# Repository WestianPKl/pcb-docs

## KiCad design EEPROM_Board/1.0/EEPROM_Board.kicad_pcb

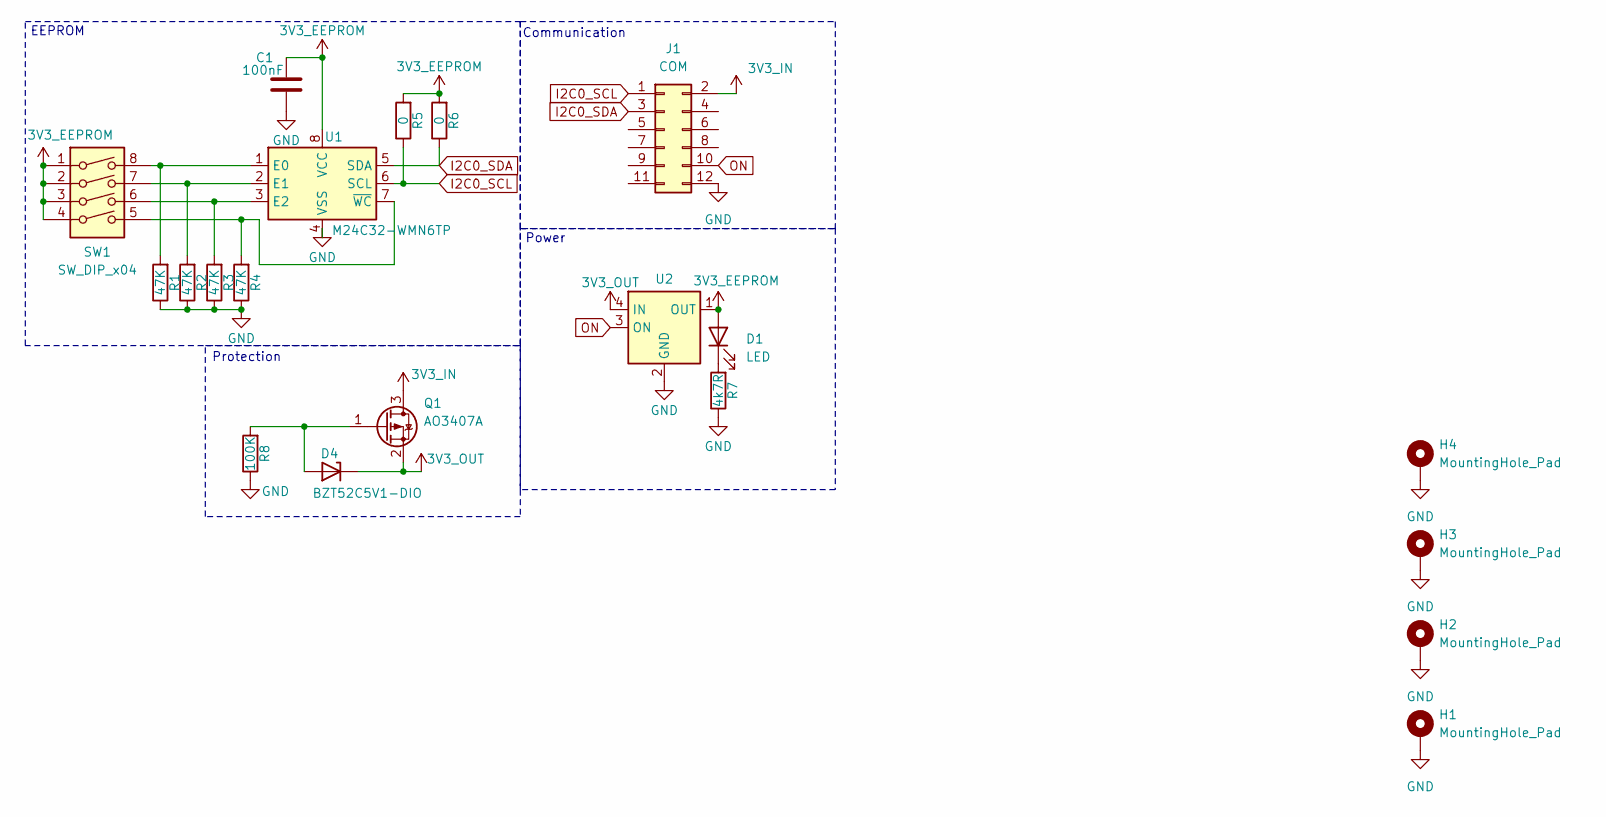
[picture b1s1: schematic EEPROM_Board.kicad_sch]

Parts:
C1: 100nF; C_0805_2012Metric
D1: LED; LED_0805_2012Metric
D4: BZT52C5V1-DIO; D_SOD-123F
H1, H2, H3, H4: MountingHole_Pad; MountingHole_3.2mm_M3_DIN965_Pad
J1: COM; PinHeader_2x06_P2.54mm_Vertical
Q1: AO3407A; SOT-23
R1, R2, R3, R4: 47K; R_0805_2012Metric
R5, R6: 0; R_0805_2012Metric
R7: 4k7R; R_0805_2012Metric
R8: 100K; R_0805_2012Metric
SW1: SW_DIP_x04; SW_DIP_SPSTx04_Slide_9.78x12.34mm_W7.62mm_P2.54mm
U1: M24C32-WMN6TP; SOIC-8_3.9x4.9mm_P1.27mm
U2: SIP32431DR3-T1GE3; SOT-363_SC-70-6

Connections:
3V3_EEPROM: C1.1, D1.2 (A), R5.2, R6.2, SW1.1, SW1.2, SW1.3, SW1.4, U1.8 (VCC), U2.1 (OUT)
3V3_IN: J1.2, Q1.3 (D)
3V3_OUT: D4.1 (K), Q1.2 (S), U2.4 (IN)
GND: C1.2, H1.1, H2.1, H3.1, H4.1, J1.12, R1.1, R2.1, R3.1, R4.1, R7.1, R8.1, U1.4 (VSS), U2.2 (GND), U2.5 (GND)
I2C0_SCL: J1.1, R5.1, U1.6 (SCL)
I2C0_SDA: J1.3, R6.1, U1.5 (SDA)
unnamed: D1.1 (K), R7.2
unnamed: D4.2 (A), Q1.1 (G), R8.2
unnamed: R1.2, SW1.8, U1.1 (E0)
unnamed: R2.2, SW1.7, U1.2 (E1)
unnamed: R3.2, SW1.6, U1.3 (E2)
unnamed: R4.2, SW1.5, U1.7 (~WC)
ON: J1.10, U2.3 (ON)

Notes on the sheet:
Communication
Power
EEPROM
Protection

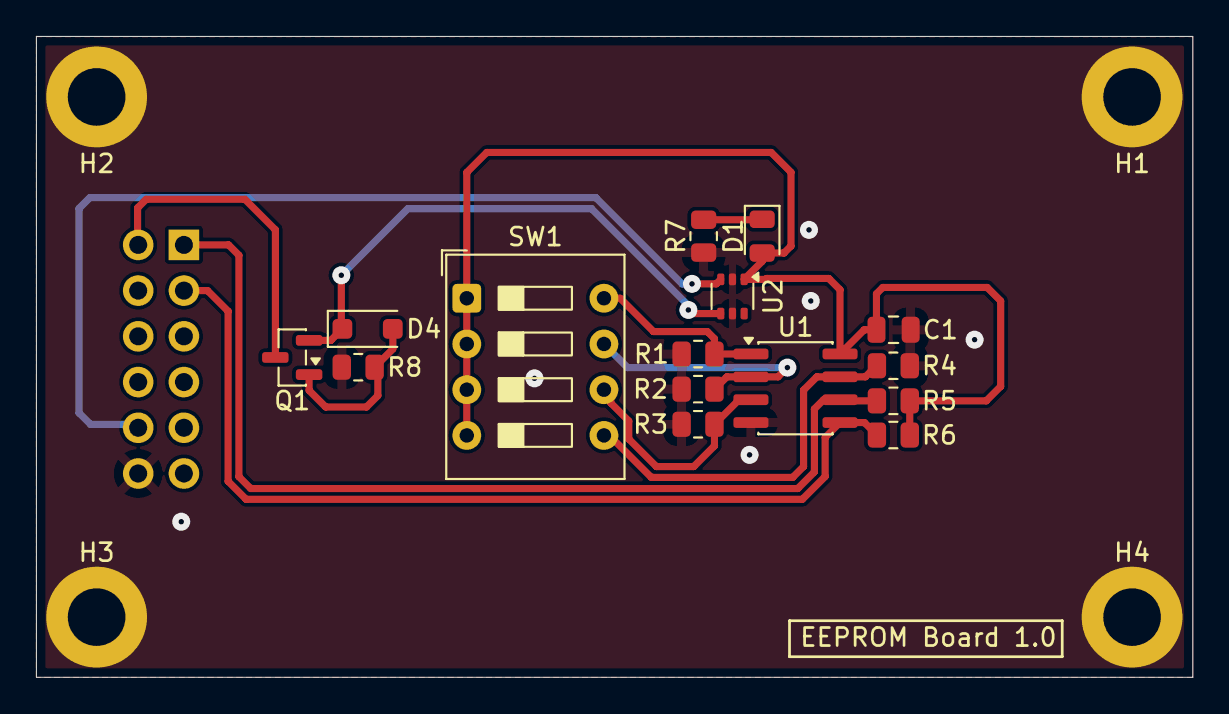
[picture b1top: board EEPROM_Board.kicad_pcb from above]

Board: 2 copper layers, 64.2 x 35.6 mm, 20 parts (1 on the bottom side), 13 nets.

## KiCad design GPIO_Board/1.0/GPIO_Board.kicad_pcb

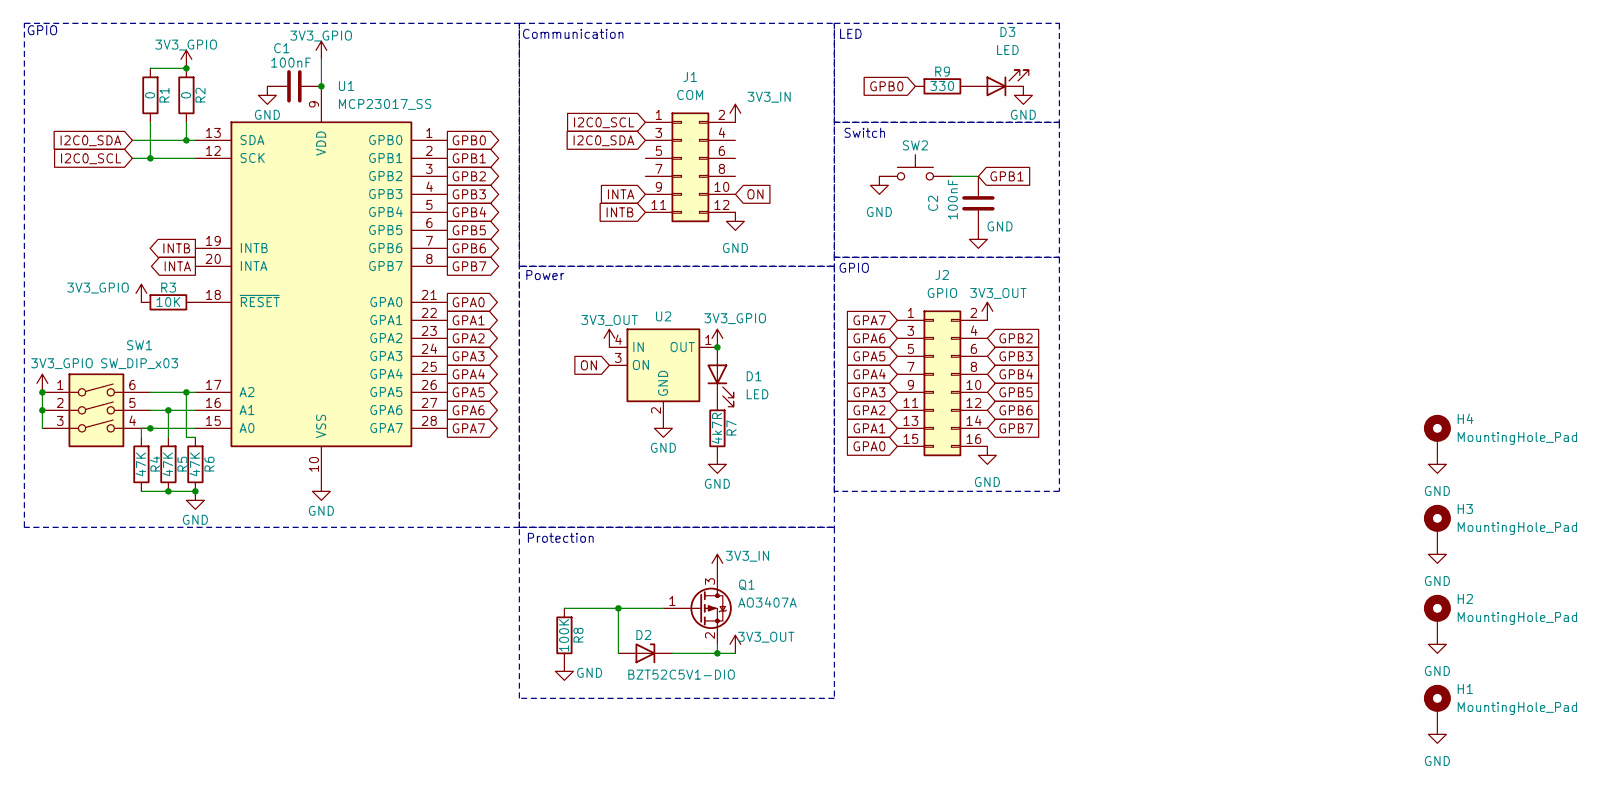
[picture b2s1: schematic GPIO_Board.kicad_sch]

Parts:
C1, C2: 100nF; C_0805_2012Metric
D1, D3: LED; LED_0805_2012Metric
D2: BZT52C5V1-DIO; D_SOD-123F
H1, H2, H3, H4: MountingHole_Pad; MountingHole_3.2mm_M3_DIN965_Pad
J1: COM; PinHeader_2x06_P2.54mm_Vertical
J2: GPIO; PinHeader_2x08_P2.54mm_Vertical
Q1: AO3407A; SOT-23
R1, R2: 0; R_0805_2012Metric
R3: 10K; R_0805_2012Metric
R4, R5, R6: 47K; R_0805_2012Metric
R7: 4k7R; R_0805_2012Metric
R8: 100K; R_0805_2012Metric
R9: 330; R_0805_2012Metric
SW1: SW_DIP_x03; SW_DIP_SPSTx03_Slide_9.78x9.8mm_W7.62mm_P2.54mm
SW2: Tact Switch 6x6mm / 13mm; SW_PUSH_6mm
U1: MCP23017_SS; SSOP-28_5.3x10.2mm_P0.65mm
U2: SIP32431DR3-T1GE3; SOT-363_SC-70-6

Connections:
3V3_GPIO: C1.1, D1.2 (A), R1.2, R2.2, R3.2, SW1.1, SW1.2, SW1.3, U1.9 (VDD), U2.1 (OUT)
3V3_IN: J1.2, Q1.3 (D)
3V3_OUT: D2.1 (K), J2.2, Q1.2 (S), U2.4 (IN)
GND: C1.2, C2.2, D3.1 (K), H1.1, H2.1, H3.1, H4.1, J1.12, J2.16, R4.1, R5.1, R6.1, R7.1, R8.1, SW2.1, U1.10 (VSS), U2.2 (GND), U2.5 (GND)
GPA0: J2.15, U1.21 (GPA0)
GPA1: J2.13, U1.22 (GPA1)
GPA2: J2.11, U1.23 (GPA2)
GPA3: J2.9, U1.24 (GPA3)
GPA4: J2.7, U1.25 (GPA4)
GPA5: J2.5, U1.26 (GPA5)
GPA6: J2.3, U1.27 (GPA6)
GPA7: J2.1, U1.28 (GPA7)
GPB0: R9.2, U1.1 (GPB0)
GPB1: C2.1, SW2.2, U1.2 (GPB1)
GPB2: J2.4, U1.3 (GPB2)
GPB3: J2.6, U1.4 (GPB3)
GPB4: J2.8, U1.5 (GPB4)
GPB5: J2.10, U1.6 (GPB5)
GPB6: J2.12, U1.7 (GPB6)
GPB7: J2.14, U1.8 (GPB7)
I2C0_SCL: J1.1, R1.1, U1.12 (SCK)
I2C0_SDA: J1.3, R2.1, U1.13 (SDA)
INTA: J1.9, U1.20 (INTA)
INTB: J1.11, U1.19 (INTB)
unnamed: D1.1 (K), R7.2
unnamed: D2.2 (A), Q1.1 (G), R8.2
unnamed: D3.2 (A), R9.1
unnamed: R4.2, SW1.4, U1.15 (A0)
unnamed: R5.2, SW1.5, U1.16 (A1)
unnamed: R6.2, SW1.6, U1.17 (A2)
unnamed: R3.1, U1.18 (~RESET)
ON: J1.10, U2.3 (ON)

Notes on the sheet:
LED
Protection
Communication
GPIO
Switch
Power

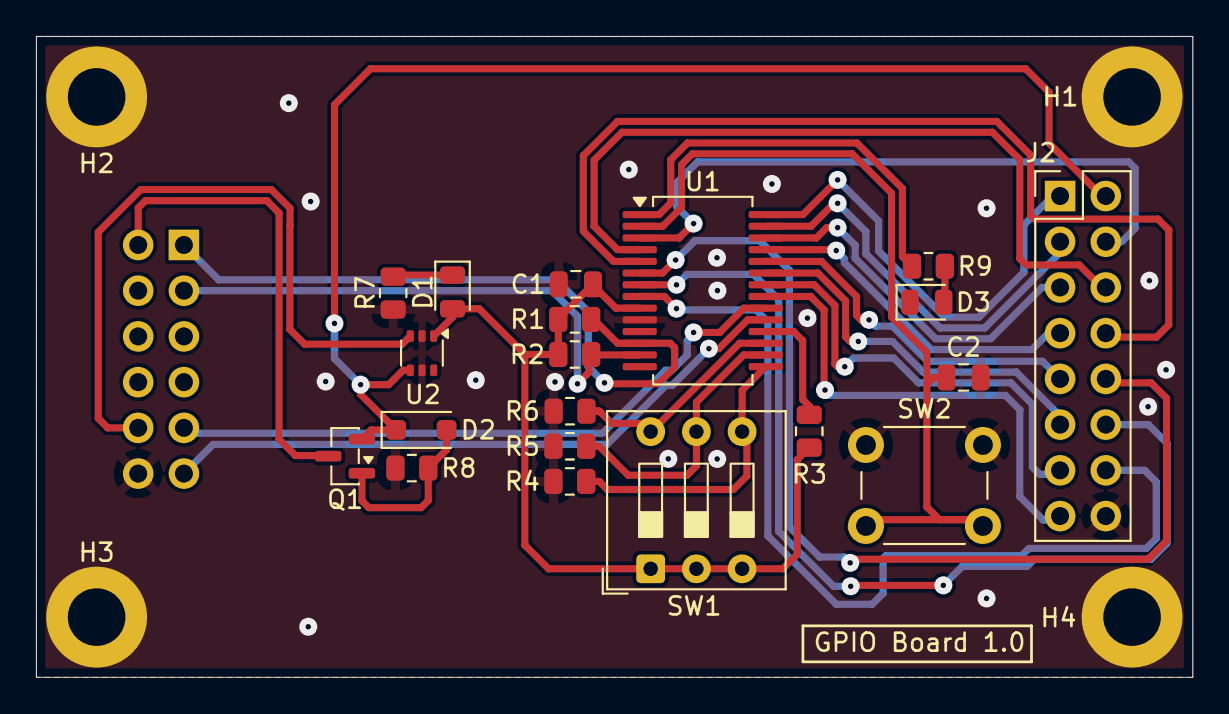
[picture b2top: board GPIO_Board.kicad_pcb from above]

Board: 2 copper layers, 64.2 x 35.6 mm, 25 parts (1 on the bottom side), 32 nets.

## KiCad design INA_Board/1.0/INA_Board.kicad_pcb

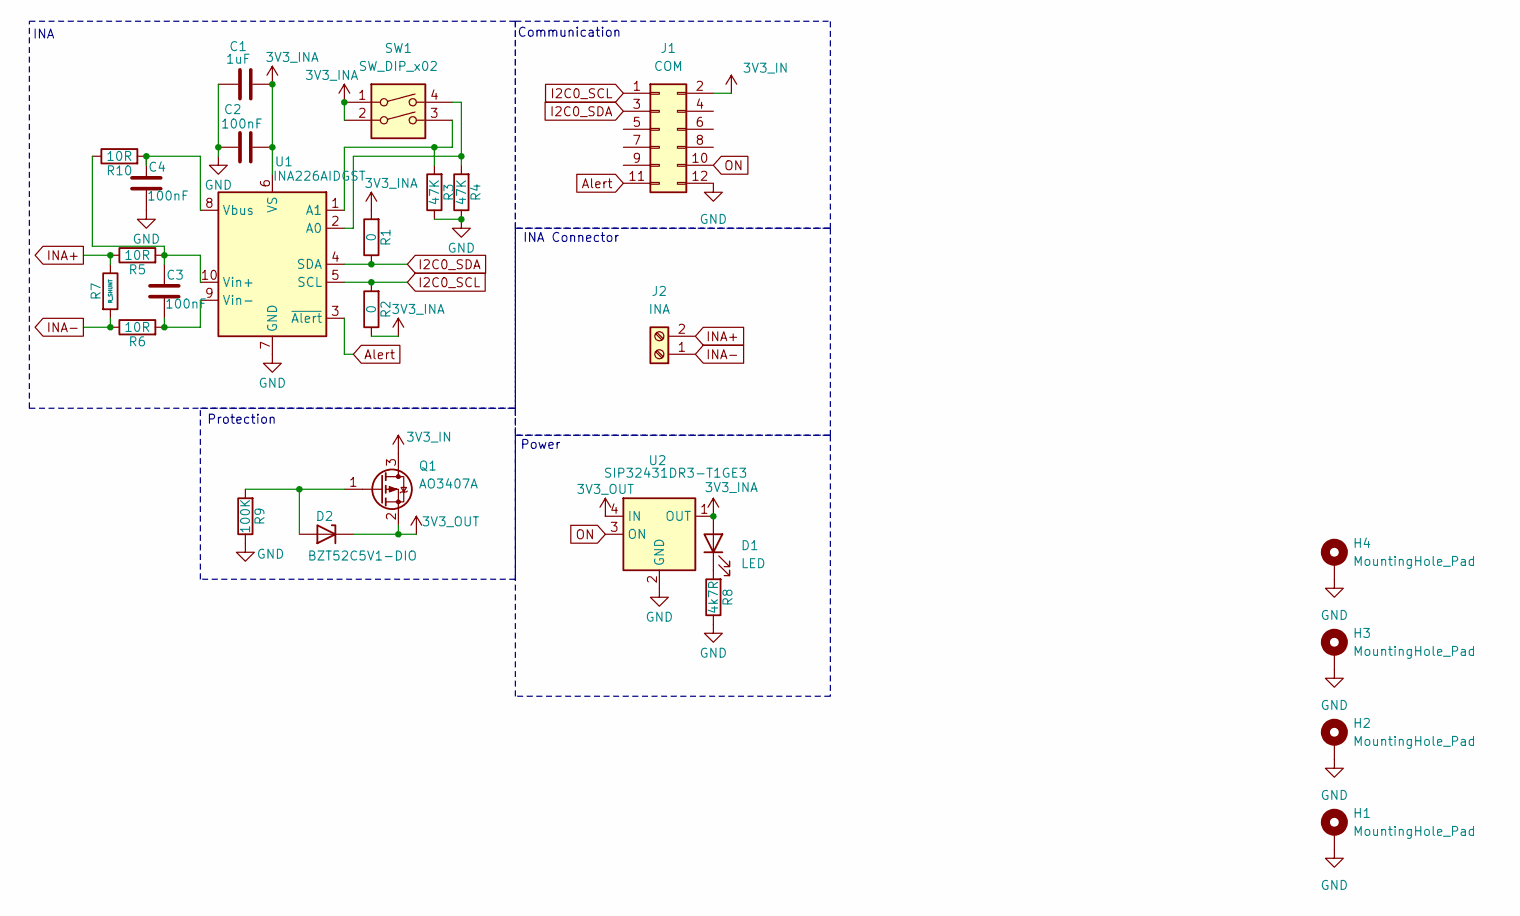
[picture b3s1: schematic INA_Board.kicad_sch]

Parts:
C1: 1uF; C_0603_1608Metric
C2, C3, C4: 100nF; C_0805_2012Metric
D1: LED; LED_0805_2012Metric
D2: BZT52C5V1-DIO; D_SOD-123F
H1, H2, H3, H4: MountingHole_Pad; MountingHole_3.2mm_M3_DIN965_Pad
J1: COM; PinHeader_2x06_P2.54mm_Vertical
J2: INA; TerminalBlock_Phoenix_MKDS-1,5-2_1x02_P5.00mm_Horizontal
Q1: AO3407A; SOT-23
R1, R2: 0; R_0805_2012Metric
R3, R4: 47K; R_0805_2012Metric
R5, R6, R10: 10R; R_0805_2012Metric
R7: R_SHUNT; R_2512_6332Metric
R8: 4k7R; R_0805_2012Metric
R9: 100K; R_0805_2012Metric
SW1: SW_DIP_x02; SW_DIP_SPSTx02_Slide_9.78x7.26mm_W7.62mm_P2.54mm
U1: INA226AIDGST; VSSOP-10_3x3mm_P0.5mm
U2: SIP32431DR3-T1GE3; SOT-363_SC-70-6

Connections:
3V3_IN: J1.2, Q1.3 (D)
3V3_INA: C1.1, C2.1, D1.2 (A), R1.2, R2.1, SW1.1, SW1.2, U1.6 (VS), U2.1 (OUT)
3V3_OUT: D2.1 (K), Q1.2 (S), U2.4 (IN)
Alert: J1.11, U1.3 (~Alert)
GND: C1.2, C2.2, C4.1, H1.1, H2.1, H3.1, H4.1, J1.12, R3.1, R4.1, R8.1, R9.1, U1.7 (GND), U2.2 (GND), U2.5 (GND)
I2C0_SCL: J1.1, R2.2, U1.5 (SCL)
I2C0_SDA: J1.3, R1.1, U1.4 (SDA)
INA+: J2.2, R5.1, R7.1
INA-: J2.1, R6.1, R7.2
unnamed: D1.1 (K), R8.2
unnamed: D2.2 (A), Q1.1 (G), R9.2
unnamed: R4.2, SW1.4, U1.2 (A0)
unnamed: R3.2, SW1.3, U1.1 (A1)
unnamed: C4.2, R10.2, U1.8 (Vbus)
unnamed: C3.2, R5.2, R10.1, U1.10 (Vin+)
unnamed: C3.1, R6.2, U1.9 (Vin-)
ON: J1.10, U2.3 (ON)

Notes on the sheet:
Protection
INA Connector
Power
INA
Communication

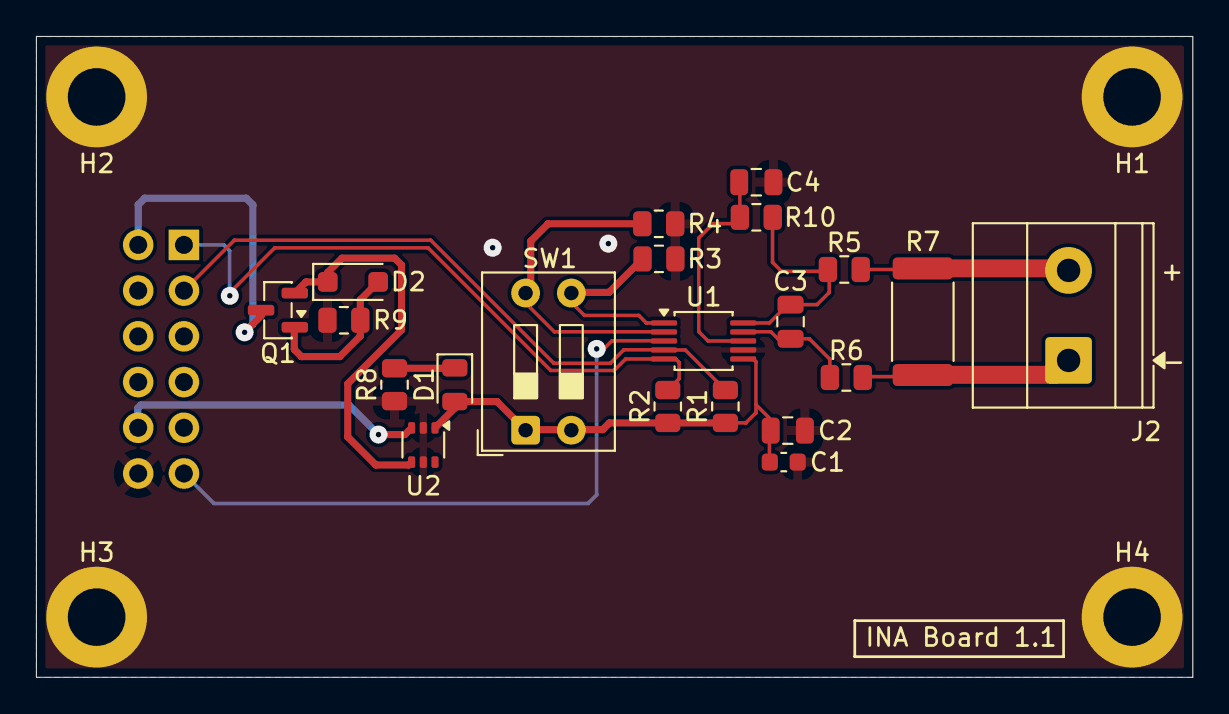
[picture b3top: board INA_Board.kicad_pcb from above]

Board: 2 copper layers, 64.2 x 35.6 mm, 26 parts (1 on the bottom side), 17 nets.

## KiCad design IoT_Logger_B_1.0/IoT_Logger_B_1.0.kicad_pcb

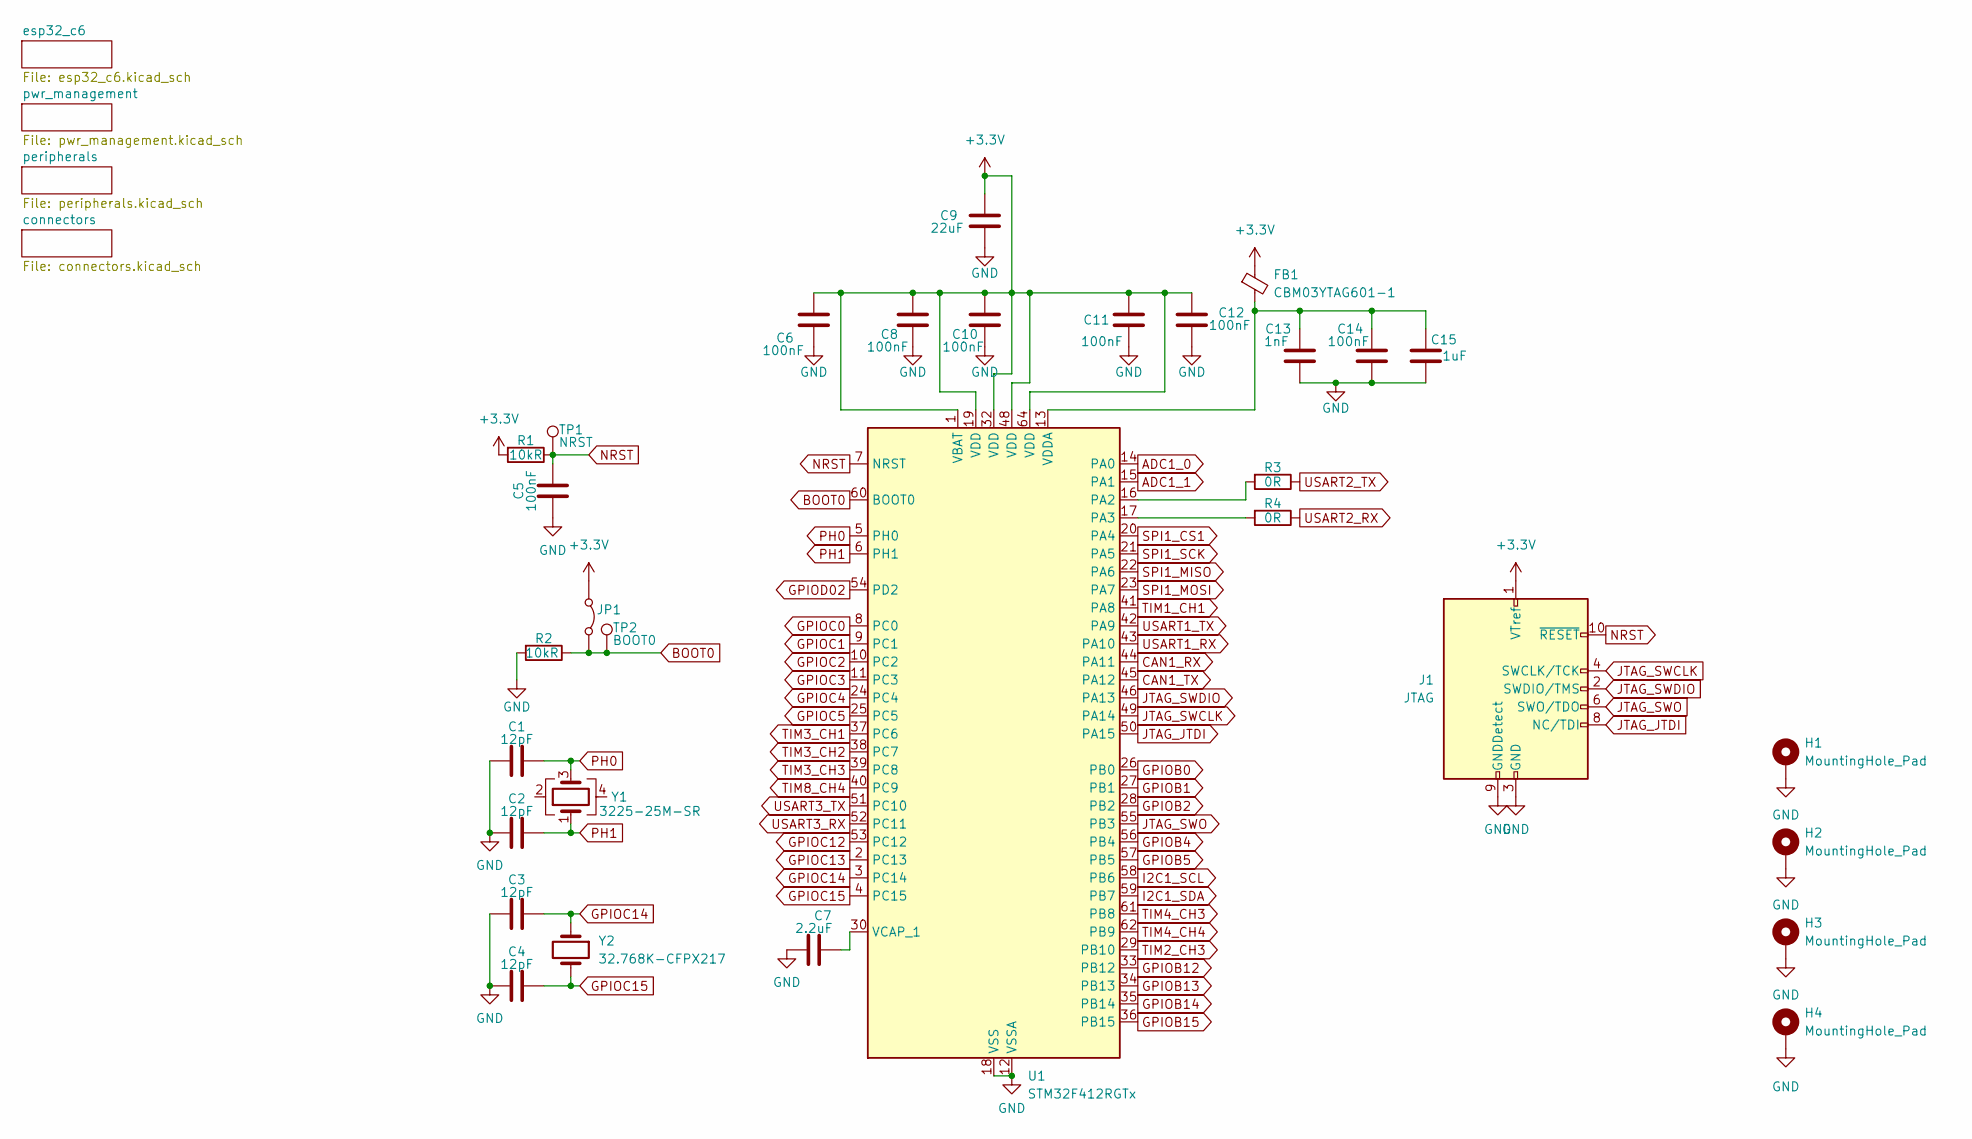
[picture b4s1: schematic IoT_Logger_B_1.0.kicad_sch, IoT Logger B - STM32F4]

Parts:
C1, C2, C3, C4: 12pF; C_0603_1608Metric
C5, C6, C8, C10, C11, C12, C14: 100nF; C_0603_1608Metric
C7: 2.2uF; C_0603_1608Metric
C9: 22uF; C_0603_1608Metric
C13: 1nF; C_0603_1608Metric
C15: 1uF; C_0603_1608Metric
FB1: CBM03YTAG601-1; L_0603_1608Metric
H1, H2, H3, H4: MountingHole_Pad; MountingHole_3.2mm_M3_DIN965_Pad
J1: JTAG; PinHeader_2x05_P1.27mm_Vertical
JP1: Jumper_2_Bridged; PinHeader_1x02_P2.54mm_Vertical
R1, R2: 10kR; R_0603_1608Metric
R3, R4: 0R; R_0603_1608Metric
TP1: NRST; TestPoint_Pad_D1.5mm
TP2: BOOT0; TestPoint_Pad_D1.5mm
U1: STM32F412RGTx; LQFP-64_10x10mm_P0.5mm
Y1: 3225-25M-SR; Crystal_SMD_3225-4Pin_3.2x2.5mm
Y2: 32.768K-CFPX217; Crystal_SMD_3215-2Pin_3.2x1.5mm

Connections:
+3.3V: C6.1, C8.1, C9.1, C10.1, C11.1, C12.1, FB1.1, J1.1 (VTref), JP1.1 (A), R1.2, U1.1 (VBAT), U1.19 (VDD), U1.32 (VDD), U1.48 (VDD), U1.64 (VDD); also elsewhere on the board
ADC1_0: U1.14 (PA0); also elsewhere on the board
ADC1_1: U1.15 (PA1); also elsewhere on the board
BOOT0: JP1.2 (B), R2.1, TP2.1, U1.60 (BOOT0); also elsewhere on the board
CAN1_RX: U1.44 (PA11); also elsewhere on the board
CAN1_TX: U1.45 (PA12); also elsewhere on the board
GND: C1.1, C2.1, C3.1, C4.1, C5.1, C6.2, C7.1, C8.2, C9.2, C10.2, C11.2, C12.2, C13.2, C14.2, C15.2, H1.1, H2.1, H3.1, H4.1, J1.3 (GND), J1.5 (GND), J1.9 (GNDDetect), R2.2, U1.12 (VSSA), U1.18 (VSS), U1.31 (VSS), U1.47 (VSS), U1.63 (VSS); also elsewhere on the board
GPIOB0: U1.26 (PB0); also elsewhere on the board
GPIOB1: U1.27 (PB1); also elsewhere on the board
GPIOB2: U1.28 (PB2); also elsewhere on the board
GPIOB4: U1.56 (PB4)
GPIOB5: U1.57 (PB5); also elsewhere on the board
GPIOB12: U1.33 (PB12); also elsewhere on the board
GPIOB13: U1.34 (PB13); also elsewhere on the board
GPIOB14: U1.35 (PB14); also elsewhere on the board
GPIOB15: U1.36 (PB15); also elsewhere on the board
GPIOC0: U1.8 (PC0); also elsewhere on the board
GPIOC1: U1.9 (PC1); also elsewhere on the board
GPIOC2: U1.10 (PC2); also elsewhere on the board
GPIOC3: U1.11 (PC3); also elsewhere on the board
GPIOC4: U1.24 (PC4); also elsewhere on the board
GPIOC5: U1.25 (PC5); also elsewhere on the board
GPIOC12: U1.53 (PC12); also elsewhere on the board
GPIOC13: U1.2 (PC13); also elsewhere on the board
GPIOC14: C3.2, U1.3 (PC14), Y2.1
GPIOC15: C4.2, U1.4 (PC15), Y2.2
GPIOD02: U1.54 (PD2)
I2C1_SCL: U1.58 (PB6); also elsewhere on the board
I2C1_SDA: U1.59 (PB7); also elsewhere on the board
JTAG_JTDI: J1.8 (NC/TDI), U1.50 (PA15)
JTAG_SWCLK: J1.4 (SWCLK/TCK), U1.49 (PA14)
JTAG_SWDIO: J1.2 (SWDIO/TMS), U1.46 (PA13)
JTAG_SWO: J1.6 (SWO/TDO), U1.55 (PB3)
NRST: C5.2, J1.10 (~RESET), R1.1, TP1.1, U1.7 (NRST); also elsewhere on the board
unnamed: R3.2, U1.16 (PA2)
unnamed: R4.2, U1.17 (PA3)
unnamed: C7.2, U1.30 (VCAP_1)
unnamed: C13.1, C14.1, C15.1, FB1.2, U1.13 (VDDA)
PH0: C1.2, U1.5 (PH0), Y1.3
PH1: C2.2, U1.6 (PH1), Y1.1
SPI1_CS1: U1.20 (PA4); also elsewhere on the board
SPI1_MISO: U1.22 (PA6); also elsewhere on the board
SPI1_MOSI: U1.23 (PA7); also elsewhere on the board
SPI1_SCK: U1.21 (PA5); also elsewhere on the board
TIM1_CH1: U1.41 (PA8); also elsewhere on the board
TIM2_CH3: U1.29 (PB10); also elsewhere on the board
TIM3_CH1: U1.37 (PC6); also elsewhere on the board
TIM3_CH2: U1.38 (PC7); also elsewhere on the board
TIM3_CH3: U1.39 (PC8); also elsewhere on the board
TIM3_CH4: U1.40 (PC9); also elsewhere on the board
TIM4_CH3: U1.61 (PB8); also elsewhere on the board
TIM4_CH4: U1.62 (PB9); also elsewhere on the board
USART1_RX: U1.43 (PA10); also elsewhere on the board
USART1_TX: U1.42 (PA9); also elsewhere on the board
USART2_RX: R4.1; also elsewhere on the board
USART2_TX: R3.1; also elsewhere on the board
USART3_RX: U1.52 (PC11)
USART3_TX: U1.51 (PC10)

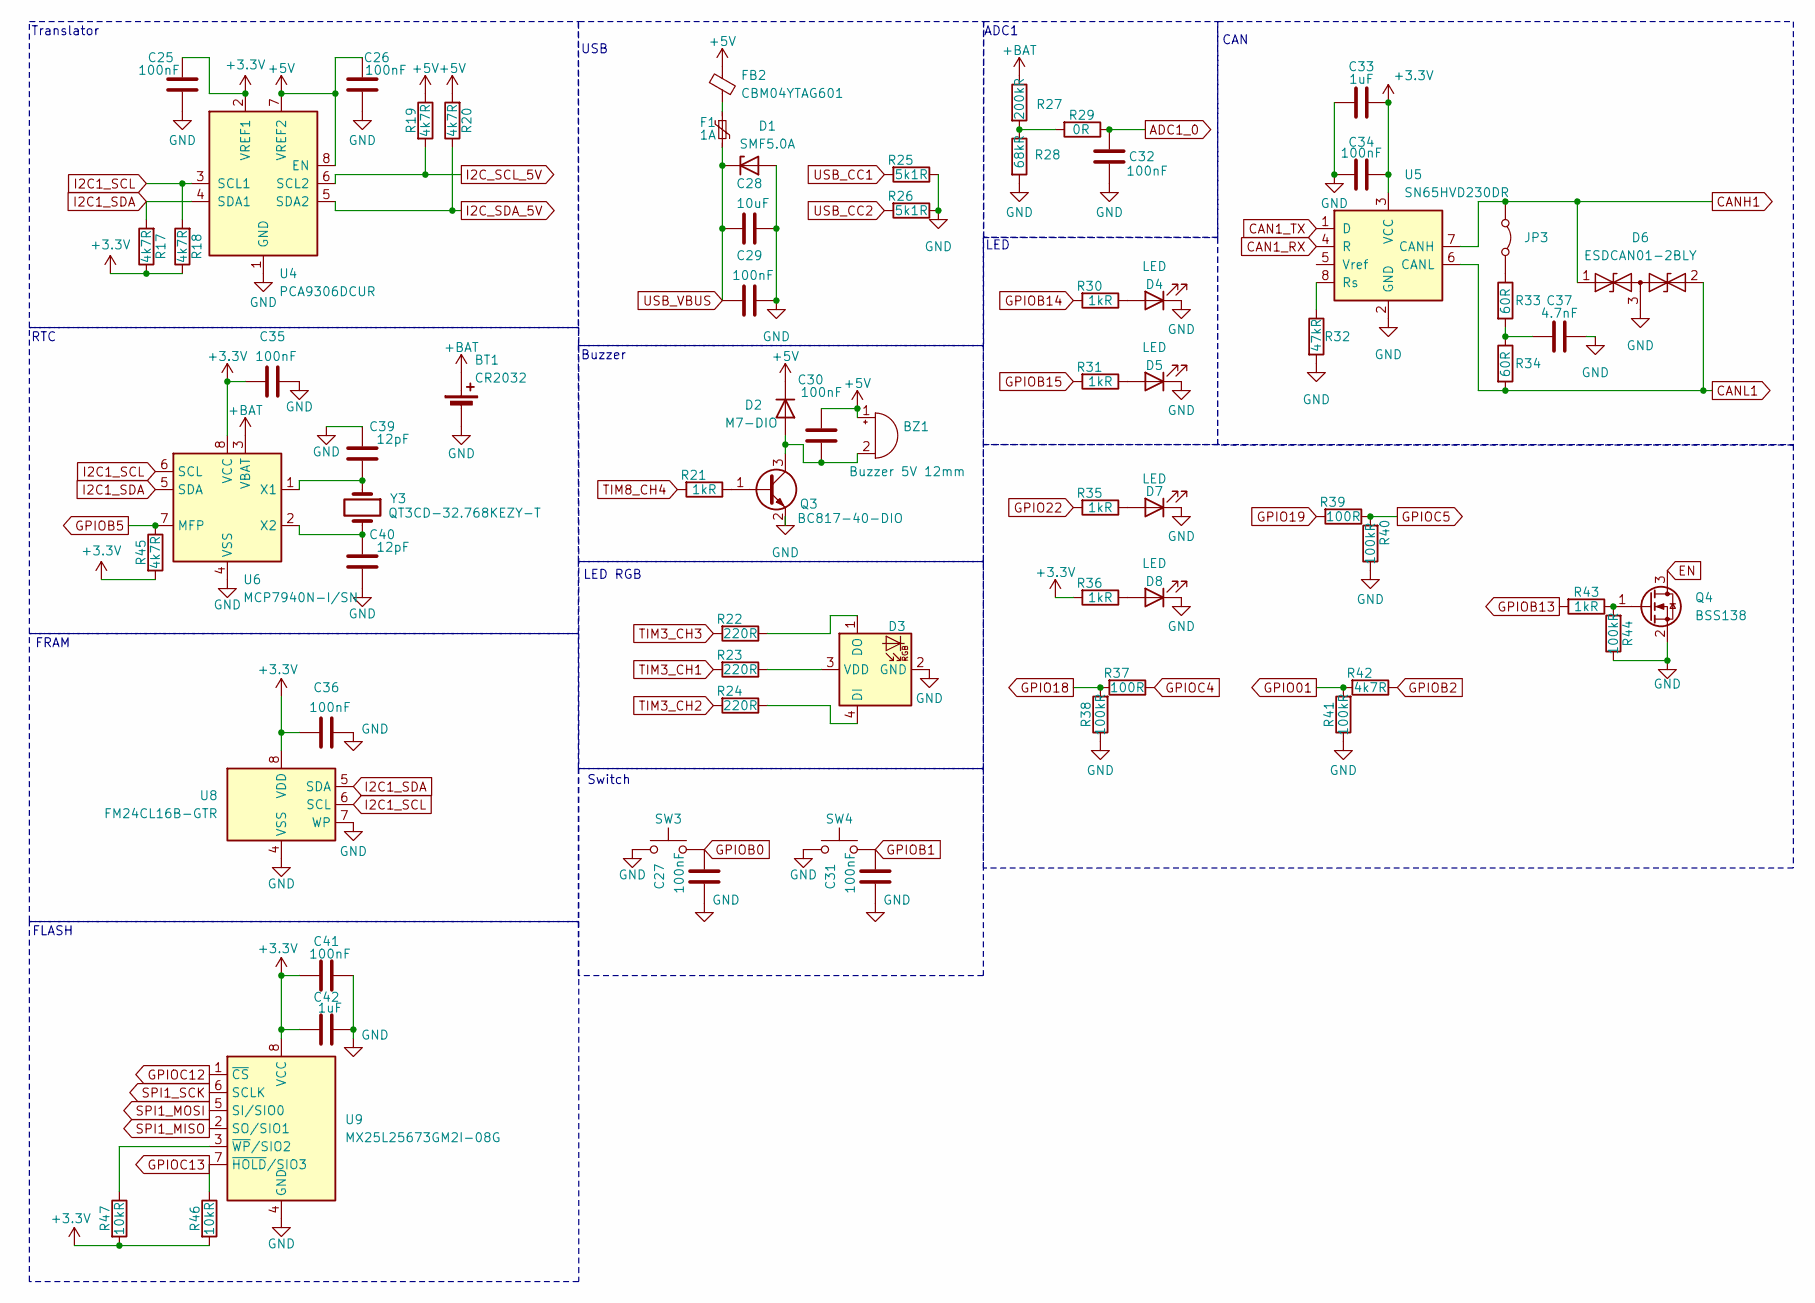
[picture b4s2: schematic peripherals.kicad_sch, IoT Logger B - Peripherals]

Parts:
BT1: CR2032; BatteryHolder_Keystone_1060_1x2032
BZ1: Buzzer 5V 12mm; Buzzer_12x9.5RM7.6
C25, C26, C27, C29, C30, C31, C32, C34, C35, C36, C41: 100nF; C_0603_1608Metric
C28: 10uF; C_0603_1608Metric
C33, C42: 1uF; C_0603_1608Metric
C37: 4.7nF; C_0603_1608Metric
C39, C40: 12pF; C_0603_1608Metric
D1: SMF5.0A; D_SOD-123F
D2: M7-DIO; D_SMA
D3: OSTBPCS2C2B; LED_Avago_PLCC4_3.2x2.8mm_CW
D4, D5, D7, D8: LED; LED_0603_1608Metric
D6: ESDCAN01-2BLY; SOT-23
F1: 1A; Fuse_1206_3216Metric
FB2: CBM04YTAG601; L_1206_3216Metric
JP3: Jumper_2_Bridged; PinHeader_1x02_P2.54mm_Vertical
Q3: BC817-40-DIO; SOT-23
Q4: BSS138; SOT-23
R17, R18, R19, R20, R42, R45: 4k7R; R_0603_1608Metric
R21, R30, R31, R35, R36, R43: 1kR; R_0603_1608Metric
R22, R23, R24: 220R; R_0603_1608Metric
R25, R26: 5k1R; R_0603_1608Metric
R27: 200kR; R_0603_1608Metric
R28: 68kR; R_0603_1608Metric
R29: 0R; R_0603_1608Metric
R32: 47kR; R_0603_1608Metric
R33, R34: 60R; R_0603_1608Metric
R37, R39: 100R; R_0603_1608Metric
R38, R40, R41, R44: 100kR; R_0603_1608Metric
R46, R47: 10kR; R_0603_1608Metric
SW3, SW4: Tact Switch 6x6mm / 13mm; SW_PUSH_6mm
U4: PCA9306DCUR; VSSOP-8_2.3x2mm_P0.5mm
U5: SN65HVD230DR; SOIC-8_3.9x4.9mm_P1.27mm
U6: MCP7940N-I/SN; SOIC-8_3.9x4.9mm_P1.27mm
U8: FM24CL16B-GTR; SOIC-8_3.9x4.9mm_P1.27mm
U9: MX25L25673GM2I-08G; SOIC-8_5.3x5.3mm_P1.27mm
Y3: QT3CD-32.768KEZY-T; Crystal_SMD_3215-2Pin_3.2x1.5mm

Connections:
+3.3V: C25.1, C33.1, C34.1, C35.2, C36.2, C41.2, C42.2, R17.1, R18.1, R36.2, R45.2, R46.2, R47.2, U4.2 (VREF1), U5.3 (VCC), U6.8 (VCC), U8.8 (VDD), U9.8 (VCC); also elsewhere on the board
+5V: BZ1.1 (+), C26.1, C30.2, D2.1 (K), FB2.1, R19.1, R20.2, U4.7 (VREF2), U4.8 (EN); also elsewhere on the board
+BAT: BT1.1 (+), R27.1, U6.3 (VBAT)
ADC1_0: C32.1, R29.1; also elsewhere on the board
CAN1_RX: U5.4 (R); also elsewhere on the board
CAN1_TX: U5.1 (D); also elsewhere on the board
CANH1: D6.1 (A1), JP3.1 (A), U5.7 (CANH); also elsewhere on the board
CANL1: D6.2 (A2), R34.2, U5.6 (CANL); also elsewhere on the board
EN: Q4.3 (D); also elsewhere on the board
GND: BT1.2 (-), C25.2, C26.2, C27.2, C28.1, C29.1, C31.2, C32.2, C33.2, C34.2, C35.1, C36.1, C37.1, C39.2, C40.1, C41.1, C42.1, D1.2 (A), D3.2 (GND), D4.1 (K), D5.1 (K), D6.3 (common), D7.1 (K), D8.1 (K), Q3.2 (E), Q4.2 (S), R25.1, R26.1, R28.2, R32.2, R38.1, R40.1, R41.1, R44.1, SW3.1, SW4.1, U4.1 (GND), U5.2 (GND), U6.4 (VSS), U8.4 (VSS), U8.7 (WP), U9.4 (GND); also elsewhere on the board
GPIO01: R41.2, R42.2; also elsewhere on the board
GPIO18: R37.2, R38.2; also elsewhere on the board
GPIO19: R39.2; also elsewhere on the board
GPIO22: R35.2; also elsewhere on the board
GPIOB0: C27.1, SW3.2; also elsewhere on the board
GPIOB1: C31.1, SW4.2; also elsewhere on the board
GPIOB2: R42.1; also elsewhere on the board
GPIOB5: R45.1, U6.7 (MFP); also elsewhere on the board
GPIOB13: R43.2; also elsewhere on the board
GPIOB14: R30.2; also elsewhere on the board
GPIOB15: R31.2; also elsewhere on the board
GPIOC4: R37.1; also elsewhere on the board
GPIOC5: R39.1, R40.2; also elsewhere on the board
GPIOC12: U9.1 (~CS); also elsewhere on the board
GPIOC13: R46.1, U9.7 (~HOLD/SIO3); also elsewhere on the board
I2C1_SCL: R18.2, U4.3 (SCL1), U6.6 (SCL), U8.6 (SCL); also elsewhere on the board
I2C1_SDA: R17.2, U4.4 (SDA1), U6.5 (SDA), U8.5 (SDA); also elsewhere on the board
I2C_SCL_5V: R19.2, U4.6 (SCL2); also elsewhere on the board
I2C_SDA_5V: R20.1, U4.5 (SDA2); also elsewhere on the board
unnamed: BZ1.2 (-), C30.1, D2.2 (A), Q3.3 (C)
unnamed: C37.2, R33.2, R34.1
unnamed: D3.4 (DI), R24.1
unnamed: D3.1 (DO), R22.1
unnamed: D3.3 (VDD), R23.1
unnamed: D4.2 (A), R30.1
unnamed: D5.2 (A), R31.1
unnamed: D7.2 (A), R35.1
unnamed: D8.2 (A), R36.1
unnamed: F1.1, FB2.2
unnamed: JP3.2 (B), R33.1
unnamed: Q3.1 (B), R21.1
unnamed: Q4.1 (G), R43.1, R44.2
unnamed: R27.2, R28.1, R29.2
unnamed: R32.1, U5.8 (Rs)
unnamed: C39.1, U6.1 (X1), Y3.1
unnamed: C40.2, U6.2 (X2), Y3.2
unnamed: R47.1, U9.3 (~WP/SIO2)
SPI1_MISO: U9.2 (SO/SIO1); also elsewhere on the board
SPI1_MOSI: U9.5 (SI/SIO0); also elsewhere on the board
SPI1_SCK: U9.6 (SCLK); also elsewhere on the board
TIM3_CH1: R23.2; also elsewhere on the board
TIM3_CH2: R24.2; also elsewhere on the board
TIM3_CH3: R22.2; also elsewhere on the board
TIM3_CH4: R21.2; also elsewhere on the board
USB_CC1: R25.2; also elsewhere on the board
USB_CC2: R26.2; also elsewhere on the board
USB_VBUS: C28.2, C29.2, D1.1 (K), F1.2; also elsewhere on the board

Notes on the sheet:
USB
CAN
Switch
FRAM
Translator
Buzzer
FLASH
LED RGB
RTC
ADC1
LED

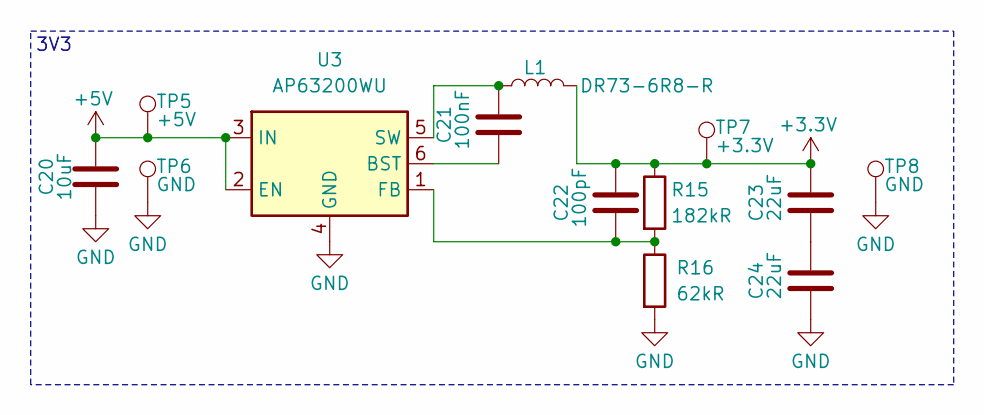
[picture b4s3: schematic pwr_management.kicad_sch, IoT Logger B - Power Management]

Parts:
C20: 10uF; C_1206_3216Metric
C21: 100nF; C_0805_2012Metric
C22: 100pF; C_0805_2012Metric
C23, C24: 22uF; C_1206_3216Metric
L1: DR73-6R8-R; L_7.3x7.3_H3.5
R15: 182kR; R_0805_2012Metric
R16: 62kR; R_0805_2012Metric
TP5: +5V; TestPoint_Pad_D1.5mm
TP6, TP8: GND; TestPoint_Pad_D1.5mm
TP7: +3.3V; TestPoint_Pad_D1.5mm
U3: AP63200WU; TSOT-23-6

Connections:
+3.3V: C22.1, C23.1, L1.2, R15.1, TP7.1; also elsewhere on the board
+5V: C20.1, TP5.1, U3.2 (EN), U3.3 (IN); also elsewhere on the board
GND: C20.2, C24.2, R16.2, TP6.1, TP8.1, U3.4 (GND); also elsewhere on the board
unnamed: C23.2, C24.1
unnamed: C21.2, U3.6 (BST)
unnamed: C22.2, R15.2, R16.1, U3.1 (FB)
unnamed: C21.1, L1.1, U3.5 (SW)

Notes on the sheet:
3V3

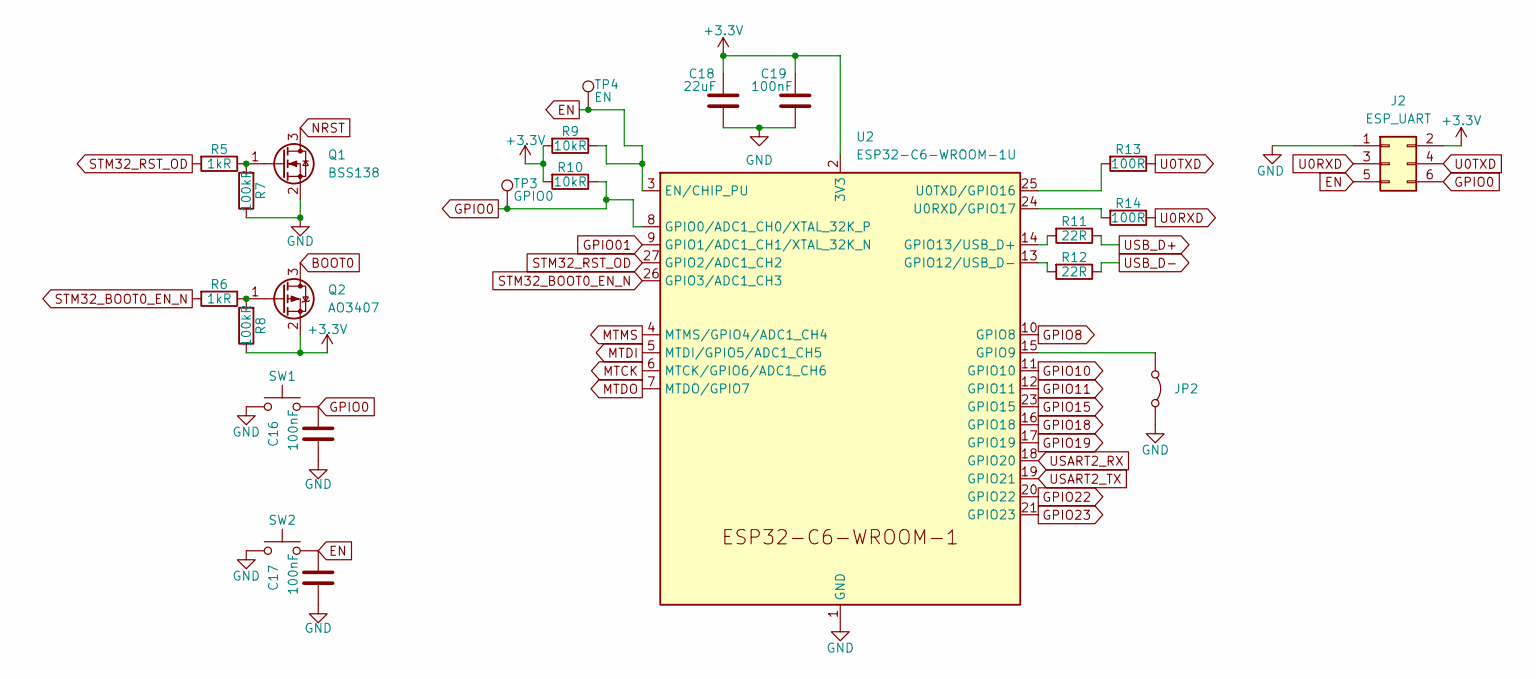
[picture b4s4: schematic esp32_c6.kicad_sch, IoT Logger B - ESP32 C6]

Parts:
C16, C17, C19: 100nF; C_0603_1608Metric
C18: 22uF; C_0603_1608Metric
J2: ESP_UART; PinHeader_2x03_P1.27mm_Vertical
JP2: Jumper_2_Bridged; PinHeader_1x02_P2.54mm_Vertical
Q1: BSS138; SOT-23
Q2: AO3407; SOT-23
R5, R6: 1kR; R_0603_1608Metric
R7, R8: 100kR; R_0603_1608Metric
R9, R10: 10kR; R_0603_1608Metric
R11, R12: 22R; R_0603_1608Metric
R13, R14: 100R; R_0603_1608Metric
SW1, SW2: Tact Switch 6x6mm / 13mm; SW_PUSH_6mm
TP3: GPIO0; TestPoint_Pad_D1.5mm
TP4: EN; TestPoint_Pad_D1.5mm
U2: ESP32-C6-WROOM-1U

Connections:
+3.3V: C18.1, C19.1, J2.2, Q2.2 (S), R8.1, R9.2, R10.2, U2.2 (3V3); also elsewhere on the board
BOOT0: Q2.3 (D); also elsewhere on the board
EN: C17.1, J2.5, R9.1, SW2.2, TP4.1, U2.3 (EN/CHIP_PU); also elsewhere on the board
GND: C16.2, C17.2, C18.2, C19.2, J2.1, JP2.2 (B), Q1.2 (S), R7.1, SW1.1, SW2.1, U2.1 (GND), U2.28 (GND), U2.29 (GND); also elsewhere on the board
GPIO0: C16.1, J2.6, R10.1, SW1.2, TP3.1, U2.8 (GPIO0/ADC1_CH0/XTAL_32K_P)
GPIO01: U2.9 (GPIO1/ADC1_CH1/XTAL_32K_N); also elsewhere on the board
GPIO8: U2.10 (GPIO8)
GPIO10: U2.11 (GPIO10)
GPIO11: U2.12 (GPIO11)
GPIO15: U2.23 (GPIO15)
GPIO18: U2.16 (GPIO18); also elsewhere on the board
GPIO19: U2.17 (GPIO19); also elsewhere on the board
GPIO22: U2.20 (GPIO22); also elsewhere on the board
GPIO23: U2.21 (GPIO23)
MTCK: U2.6 (MTCK/GPIO6/ADC1_CH6)
MTDI: U2.5 (MTDI/GPIO5/ADC1_CH5)
MTDO: U2.7 (MTDO/GPIO7)
MTMS: U2.4 (MTMS/GPIO4/ADC1_CH4)
NRST: Q1.3 (D); also elsewhere on the board
unnamed: JP2.1 (A), U2.15 (GPIO9)
unnamed: Q1.1 (G), R5.1, R7.2
unnamed: Q2.1 (G), R6.1, R8.2
unnamed: R12.2, U2.13 (GPIO12/USB_D-)
unnamed: R11.2, U2.14 (GPIO13/USB_D+)
unnamed: R14.2, U2.24 (U0RXD/GPIO17)
unnamed: R13.2, U2.25 (U0TXD/GPIO16)
STM32_BOOT0_EN_N: R6.2, U2.26 (GPIO3/ADC1_CH3)
STM32_RST_OD: R5.2, U2.27 (GPIO2/ADC1_CH2)
U0RXD: J2.3, R14.1
U0TXD: J2.4, R13.1
USART2_RX: U2.18 (GPIO20); also elsewhere on the board
USART2_TX: U2.19 (GPIO21); also elsewhere on the board
USB_D+: R11.1; also elsewhere on the board
USB_D-: R12.1; also elsewhere on the board
